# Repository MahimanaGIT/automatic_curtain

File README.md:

<h1 align="center">Automatic Curtain</h1>

<div align="center">
Elevate your home with IoT-enabled smart curtain controller for effortless living
</div>

## ⭐️ Why Automatic Curtain?
Automating blinds can provide convenience and energy efficiency. They can be programmed to open and close at specific times of the day, allowing natural light in to reduce the need of artificial lighting. They can also be controlled remotely, making it easy to adjust the amount of light and privacy in a room without having to physically adjust the blinds. Additionally, automatic blinds can help to regulate the temperature in a room.

## 🔥 Watch the video

<p align="center">
  
</p>

## ✨ Features

- 😎 Easy to set up and integrate
- 📱 Remote control - the ability to open and close the curtains with precision using Alexa app
- 🛡 Safety feature - the ability to detect obstacles and stop the motor to prevent injury or damage to the curtains
- 💅 Manual Override - the ability to manually operate the curtains in case of Alexa not available
- 🚀 Motorized operation - the ability to open and close the curtains using a motor, rather than manual operation
- 📦 Smart home integration - the ability to connect the blinds to other smart home devices such as thermostat using alexa. Provides added convenience and energy efficiency

## 📋 [Doxygen Documentation](https://mahimanagit.github.io/automatic_curtain/)

## 🚀 Getting Started
### For how to use and build your own, refer [🗒 Manual](resources/MANUAL/manual.pdf)
### 👨‍💻 [Coding Style](https://google.github.io/styleguide/cppguide.html)
### Steps to setup for development:
1. Clone the repo
2. Setup clang format:
   - Install clang format extension in VS Code: 
    ```
      Name: Clang-Format
      Id: xaver.clang-format
      Description: Use Clang-Format in Visual Studio Code
      Version: 1.9.0
      Publisher: xaver
      VS Marketplace Link: https://marketplace.visualstudio.com/items?itemName=xaver.clang-format
    ```
   - Add following lines to **settings.json** in your VS Code:
    ```
    "editor.formatOnSave": true
    ```
    Now, everytime you save your code will automatically be formatted according to clang
    
3. Setup ESP32 Arduino Core using [this guide](https://randomnerdtutorials.com/installing-the-esp32-board-in-arduino-ide-windows-instructions/)
   
4. Setup Libraries
   - The link to all the libraries can be found at the end of this page. A compressed folder of all the libraries can be found in the [folder](resources/LIBRARY_ZIP/ac_lib.zip)
   - You can download the libraries using the links or just copy the extracted libraries from the above compressed folder in the **~/Arduino/libraries** or your customized library folder.

### Optional setup for development:
1. Setup doxygen:
   - Install doxygen and graphviz (doxygen uses dot from graphviz to generate graphs):
      ```
      sudo apt-get install doxygen
      sudo apt-get install graphviz 
      ```
   - Currently, the **DOT_PATH** is hardcoded in **Doxyfile** as `/usr/bin/dot` on line no. 2398, one can check if the dot path in their system is same or not by running
      ```
      which dot
      ```
      If the path is different, update it in the doxyfile
   - Generate doxygen files by running the following command in the terminal:
      ```
      doxygen Doxyfile
      ```
    - The files will be available in `doxygen` folder, click on or open `index.html` in **html** folder with any browser and you would be able to browse the documentation

## 🛡️ License

Automatic Curtain is licensed under the MIT License - see the [LICENSE](LICENSE.md) file for details.

## 🗒 References:

Thanks to the following repos for making the journey easier for the project:

1. [AsyncTCP](https://github.com/me-no-dev/AsyncTCP.git)
2. [Fauxmo](https://github.com/vintlabs/fauxmoESP.git)
3. [ESPAsyncWebServer](https://github.com/me-no-dev/ESPAsyncWebServer.git)
4. [FastLED](https://github.com/FastLED/FastLED.git)
5. [TMCStepper](https://github.com/teemuatlut/TMCStepper.gi)

For awesome readme help, referenced [novu](https://github.com/novuhq/novu)

## ✏️ Contributors 

- Dhiraj Deshmukh (deshmukhdhiraj15@gmail.com)
- Mahimana Bhatt (mahimanabhatt@gmail.com)

## 💻 Need Help?

We are more than happy to help you. If you are getting any errors or facing problems while working on this project, join our [slack](https://join.slack.com/t/mad-myj2315/shared_invite/zt-1n3oqsv1z-pdAomyv074gVCvfYfFaRgA) and ask for help. We are open to discussing anything related to the project.

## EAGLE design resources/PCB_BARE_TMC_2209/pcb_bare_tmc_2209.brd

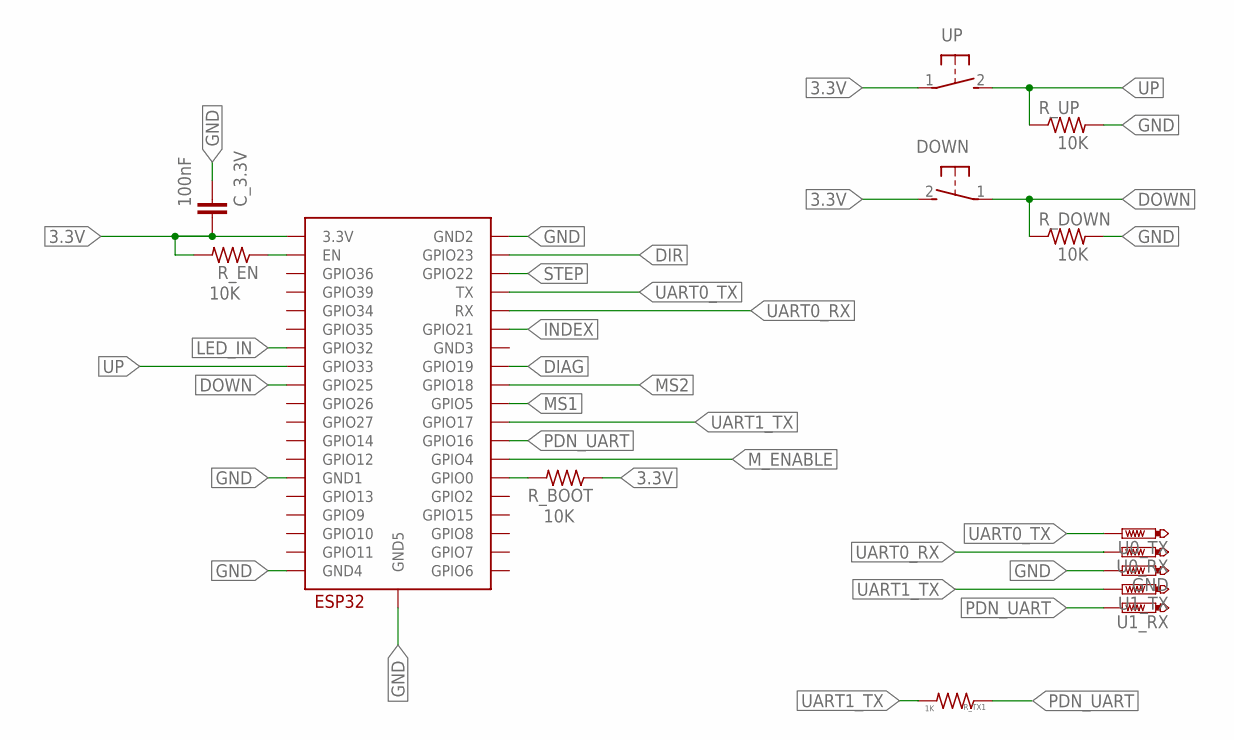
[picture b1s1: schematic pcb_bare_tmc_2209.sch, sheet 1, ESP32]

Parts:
C_3.3V: 100nF; C0805K
DOWN: 31-XX; B3F-31XX
GND: PTR1TP20SQ; TP20SQ
R_BOOT: 10K; R0805
R_DOWN: 10K; R0805
R_EN: 10K; R0805
R_TX1: 1K; R0805
R_UP: 10K; R0805
U0_RX, U0_TX, U1_RX, U1_TX: PTR1TP20SQ; TP20SQ
U$2: ESP32-WROOM
UP: 31-XX; B3F-31XX

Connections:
3.3V: C_3.3V.2, DOWN.2 (S), R_BOOT.1, R_EN.2, U$2.3V3 (3.3V), UP.1; also elsewhere on the board
DIAG: U$2.IO19 (GPIO19); also elsewhere on the board
DIR: U$2.IO23 (GPIO23); also elsewhere on the board
DOWN: DOWN.1, R_DOWN.1, U$2.IO25 (GPIO25)
GND: C_3.3V.1, GND.TP, R_DOWN.2, R_UP.2, U$2.GND1, U$2.GND2, U$2.GND4, U$2.GND5; also elsewhere on the board
INDEX: U$2.IO21 (GPIO21); also elsewhere on the board
LED_IN: U$2.IO32 (GPIO32); also elsewhere on the board
MS1: U$2.IO5 (GPIO5); also elsewhere on the board
MS2: U$2.IO18 (GPIO18); also elsewhere on the board
M_ENABLE: U$2.IO4 (GPIO4); also elsewhere on the board
unnamed: R_BOOT.2, U$2.IO0 (GPIO0)
unnamed: R_EN.1, U$2.EN
PDN_UART: R_TX1.1, U1_RX.TP, U$2.IO16 (GPIO16); also elsewhere on the board
STEP: U$2.IO22 (GPIO22); also elsewhere on the board
UART0_RX: U0_RX.TP, U$2.RX
UART0_TX: U0_TX.TP, U$2.TX
UART1_TX: R_TX1.2, U1_TX.TP, U$2.IO17 (GPIO17)
UP: R_UP.1, U$2.IO33 (GPIO33), UP.2 (S)

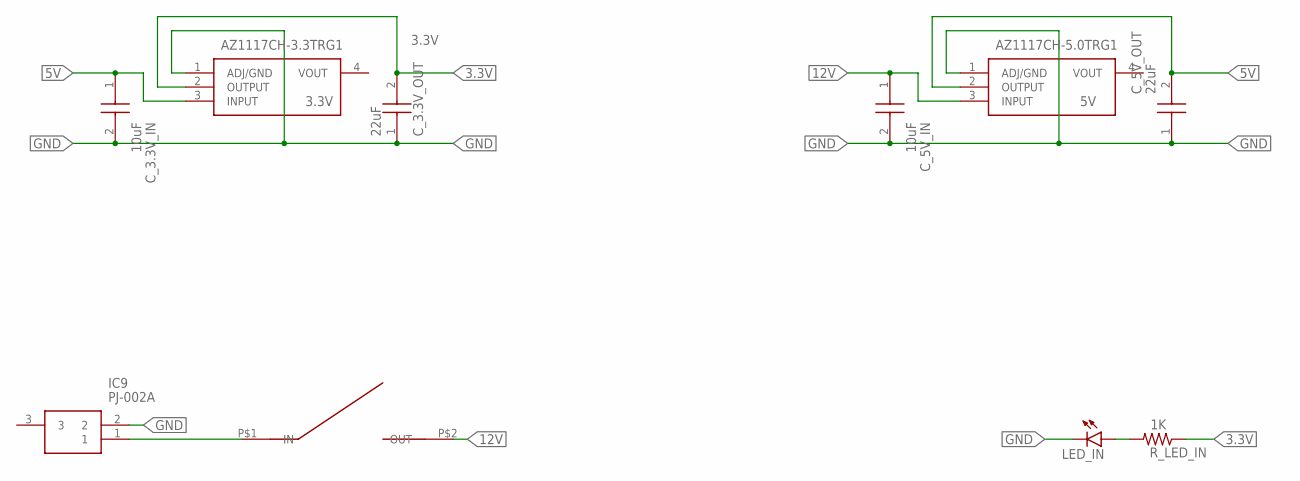
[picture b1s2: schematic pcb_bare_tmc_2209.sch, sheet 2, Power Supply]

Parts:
3.3V: AZ1117CH-3.3TRG1; SOT230P700X180-4N
5V: AZ1117CH-5.0TRG1; SOT230P700X180-4N
C_3.3V_IN, C_5V_IN: 10uF; CAPC2013X95N
C_3.3V_OUT, C_5V_OUT: 22uF; CAPC3216X100N
IC9: PJ-002A; PJ002A
LED_IN: LEDSML0805; SML0805
R_LED_IN: 1K; R0805
U$1: SPSTROCKERSWITCH2PIN; SPST2PINROCKER

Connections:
3.3V: 3.3V.2 (OUTPUT), C_3.3V_OUT.2, R_LED_IN.1; also elsewhere on the board
5V: 3.3V.3 (INPUT), 5V.2 (OUTPUT), C_3.3V_IN.1, C_5V_OUT.2; also elsewhere on the board
12V: 5V.3 (INPUT), C_5V_IN.1, U$1.P$2 (OUT); also elsewhere on the board
GND: 3.3V.1 (ADJ/GND), 5V.1 (ADJ/GND), C_3.3V_IN.2, C_3.3V_OUT.1, C_5V_IN.2, C_5V_OUT.1, IC9.2, LED_IN.C; also elsewhere on the board
unnamed: IC9.1, U$1.P$1 (IN)
unnamed: LED_IN.A, R_LED_IN.2

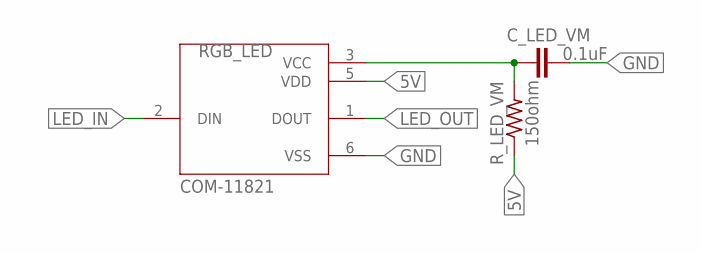
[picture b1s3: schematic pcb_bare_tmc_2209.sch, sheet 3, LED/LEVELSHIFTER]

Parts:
C_LED_VM: 0.1uF; C0805K
RGB_LED: COM-11821; LED_COM-11821
R_LED_VM: 150ohm; R0805

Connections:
5V: RGB_LED.5 (VDD), R_LED_VM.1; also elsewhere on the board
GND: C_LED_VM.2, RGB_LED.6 (VSS); also elsewhere on the board
LED_IN: RGB_LED.2 (DIN); also elsewhere on the board
LED_OUT: RGB_LED.1 (DOUT)
unnamed: C_LED_VM.1, RGB_LED.3 (VCC), R_LED_VM.2

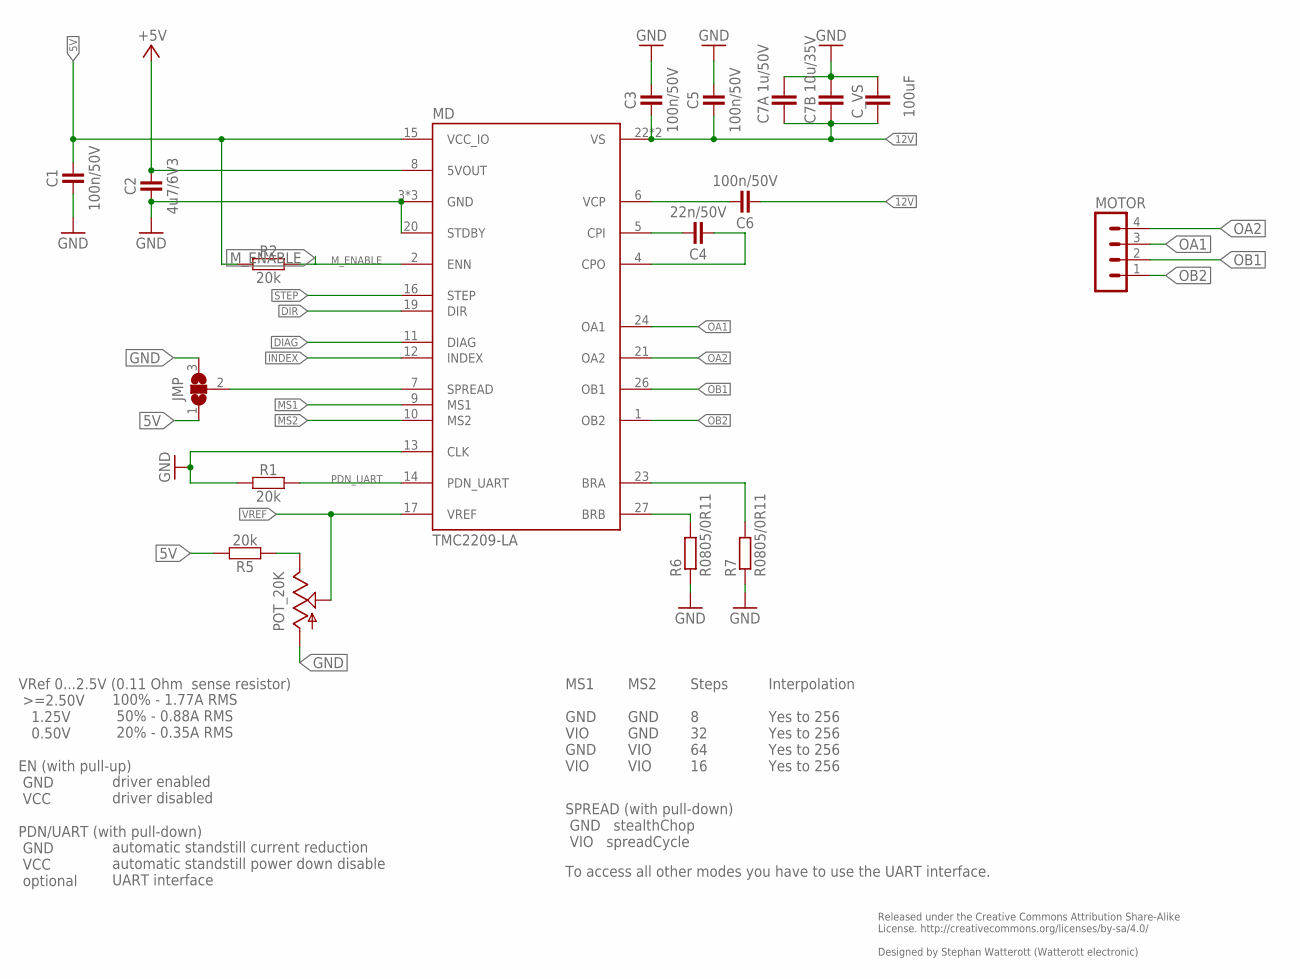
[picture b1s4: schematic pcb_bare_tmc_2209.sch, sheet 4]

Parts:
C1, C3, C5, C6: 100n/50V; C0402
C2: 4u7/6V3; C0402
C4: 22n/50V; C0402
C7A: 1u/50V; C0805
C7B: 10u/35V; C1206
C_VS: 100uF; C2.5-3
JMP: JUMPER3-0402-NC; JUMPER3-0402_NC
MD: TMC2209-LA; QFN28-PAD3.7
MOTOR: MA04-1
POT_20K: TRIM_US-3223G; 3223G
R1, R2, R5: 20k; C0402
R6, R7: R0805/0R11; M0805

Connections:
5V: C1.2, JMP.1, MD.15 (VCC_IO), R2.1, R5.2; also elsewhere on the board
12V: C3.1, C5.1, C6.1, C7A.1, C7B.1, C_VS.1, MD.22 (VS), MD.28 (VS); also elsewhere on the board
+5V: C2.2, MD.8 (5VOUT)
BRA: MD.23 (BRA), R7.2
BRB: MD.27 (BRB), R6.2
CPI: C4.2, MD.5 (CPI)
CPO: C4.1, MD.4 (CPO)
DIAG: MD.11 (DIAG); also elsewhere on the board
DIR: MD.19 (DIR); also elsewhere on the board
GND: C1.1, C2.1, C3.2, C5.2, C7A.2, C7B.2, C_VS.2, JMP.3, MD.3 (GND), MD.13 (CLK), MD.18 (GND), MD.20 (STDBY), MD.TP (GND), POT_20K.1 (A), R1.1, R6.1, R7.1; also elsewhere on the board
INDEX: MD.12 (INDEX); also elsewhere on the board
MS1: MD.9 (MS1); also elsewhere on the board
MS2: MD.10 (MS2); also elsewhere on the board
M_ENABLE: MD.2 (ENN), R2.2; also elsewhere on the board
unnamed: JMP.2, MD.7 (SPREAD)
OA1: MD.24 (OA1), MOTOR.3
OA2: MD.21 (OA2), MOTOR.4
OB1: MD.26 (OB1), MOTOR.2
OB2: MD.1 (OB2), MOTOR.1
PDN_UART: MD.14 (PDN_UART), R1.2; also elsewhere on the board
STEP: MD.16 (STEP); also elsewhere on the board
VCP: C6.2, MD.6 (VCP)
VREF: MD.17 (VREF), POT_20K.2 (S)
VREF1: POT_20K.3 (E), R5.1

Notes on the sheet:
Released under the Creative Commons Attribution Share-Alike License. http://creativecommons.org/licenses/by-sa/4.0/ Designed by Stephan Watterott (Watterott electronic)
VRef 0...2.5V (0.11 Ohm sense resistor) >=2.50V 1.25V 0.50V EN (with pull-up) GND VCC PDN/UART (with pull-down) GND VCC optional
100% - 1.77A RMS 50% - 0.88A RMS 20% - 0.35A RMS driver enabled driver disabled automatic standstill current reduction automatic standstill power down disable UART interface
MS1 GND VIO GND VIO
MS2 GND GND VIO VIO
Steps 8 32 64 16
Interpolation Yes to 256 Yes to 256 Yes to 256 Yes to 256
SPREAD (with pull-down) GND stealthChop VIO spreadCycle
To access all other modes you have to use the UART interface.

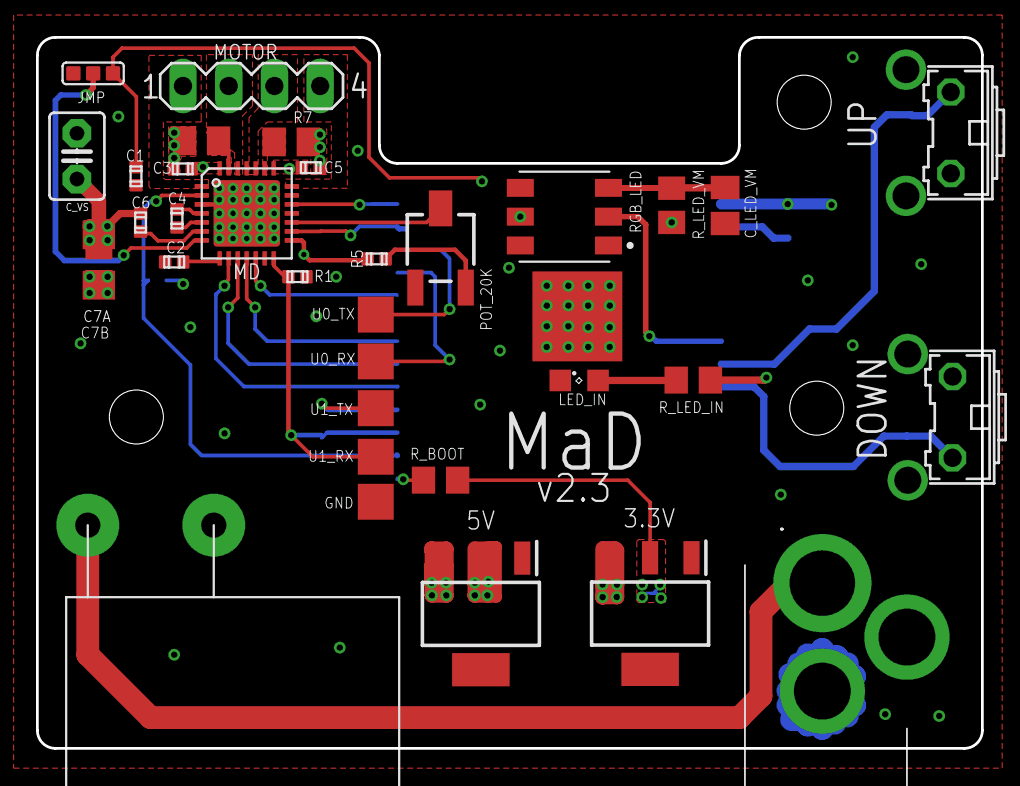
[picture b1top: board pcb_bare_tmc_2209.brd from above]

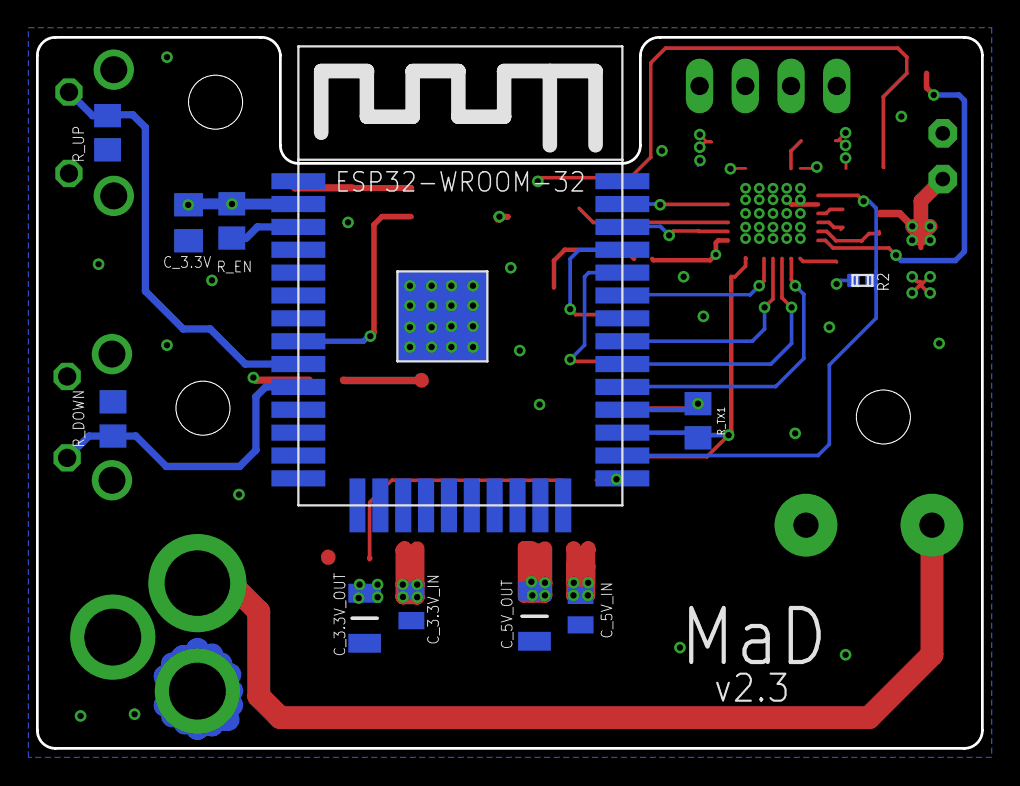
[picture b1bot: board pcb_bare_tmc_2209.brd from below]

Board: 4 copper layers, 52.5 x 39.5 mm, 45 parts (11 on the bottom side), 36 nets.

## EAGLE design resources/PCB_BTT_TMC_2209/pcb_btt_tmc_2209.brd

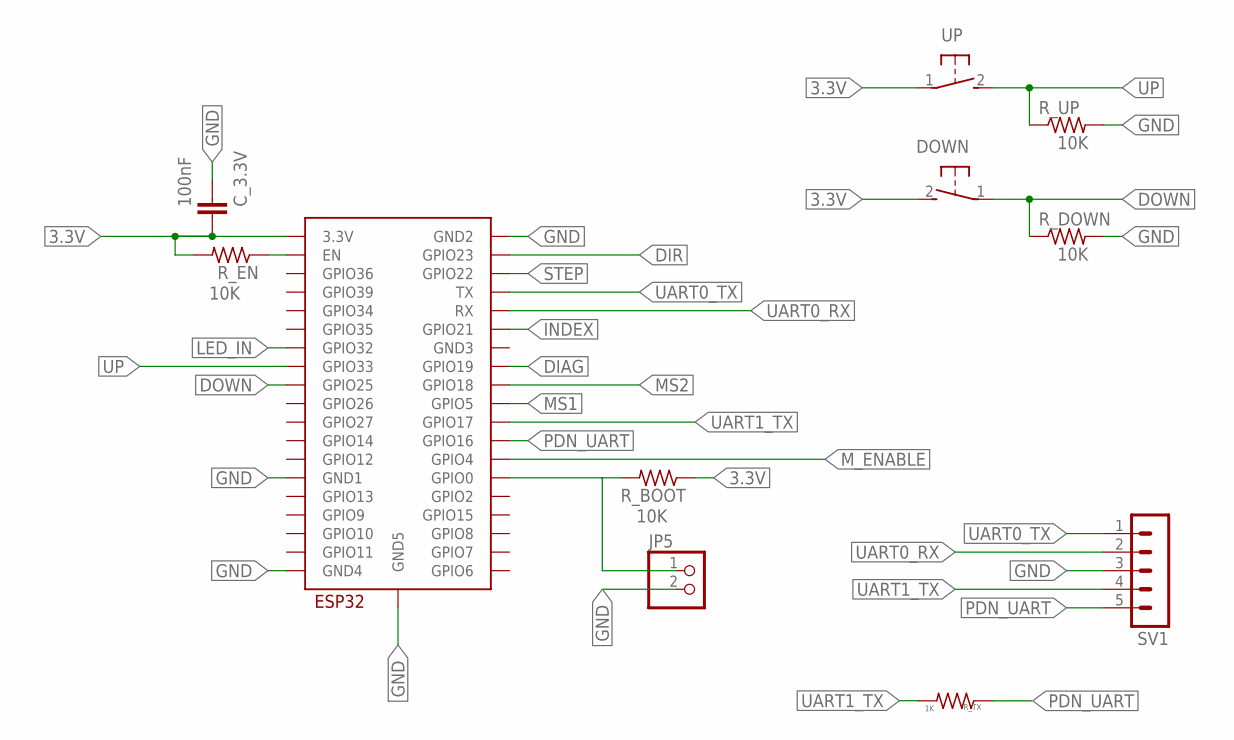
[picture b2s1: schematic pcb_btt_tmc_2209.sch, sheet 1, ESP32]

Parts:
C_3.3V: 100nF; C0805K
DOWN: 31-XX; B3F-31XX
JP5: PINHD-1X2; 1X02
R_BOOT: 10K; R0805
R_DOWN: 10K; R0805
R_EN: 10K; R0805
R_TX: 1K; R0805
R_UP: 10K; R0805
SV1: MA05-1
U$2: ESP32-WROOM
UP: 31-XX; B3F-31XX

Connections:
3.3V: C_3.3V.2, DOWN.2 (S), R_BOOT.1, R_EN.2, U$2.3V3 (3.3V), UP.1; also elsewhere on the board
DIAG: U$2.IO19 (GPIO19); also elsewhere on the board
DIR: U$2.IO23 (GPIO23); also elsewhere on the board
DOWN: DOWN.1, R_DOWN.1, U$2.IO25 (GPIO25)
GND: C_3.3V.1, JP5.2, R_DOWN.2, R_UP.2, SV1.3, U$2.GND1, U$2.GND2, U$2.GND4, U$2.GND5; also elsewhere on the board
INDEX: U$2.IO21 (GPIO21); also elsewhere on the board
LED_IN: U$2.IO32 (GPIO32); also elsewhere on the board
MS1: U$2.IO5 (GPIO5); also elsewhere on the board
MS2: U$2.IO18 (GPIO18); also elsewhere on the board
M_ENABLE: U$2.IO4 (GPIO4); also elsewhere on the board
unnamed: JP5.1, R_BOOT.2, U$2.IO0 (GPIO0)
unnamed: R_EN.1, U$2.EN
PDN_UART: R_TX.1, SV1.5, U$2.IO16 (GPIO16); also elsewhere on the board
STEP: U$2.IO22 (GPIO22); also elsewhere on the board
UART0_RX: SV1.2, U$2.RX
UART0_TX: SV1.1, U$2.TX
UART1_TX: R_TX.2, SV1.4, U$2.IO17 (GPIO17)
UP: R_UP.1, U$2.IO33 (GPIO33), UP.2 (S)

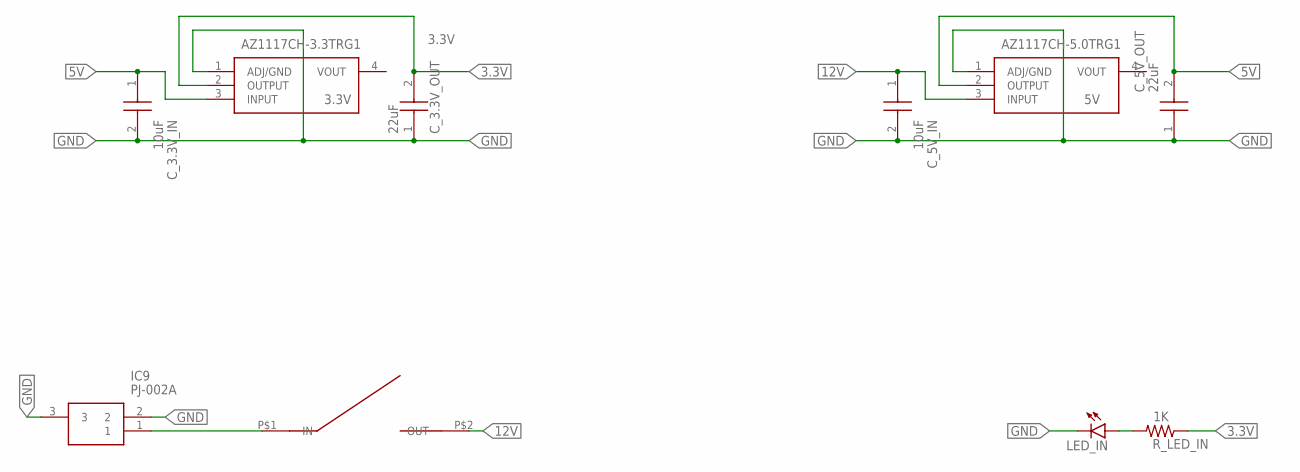
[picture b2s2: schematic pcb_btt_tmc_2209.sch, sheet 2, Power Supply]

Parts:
3.3V: AZ1117CH-3.3TRG1; SOT230P700X180-4N
5V: AZ1117CH-5.0TRG1; SOT230P700X180-4N
C_3.3V_IN, C_5V_IN: 10uF; CAPC2013X95N
C_3.3V_OUT, C_5V_OUT: 22uF; CAPC3216X100N
IC9: PJ-002A; PJ002A
LED_IN: LEDSML0805; SML0805
R_LED_IN: 1K; R0805
U$1: SPSTROCKERSWITCH2PIN; SPST2PINROCKER

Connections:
3.3V: 3.3V.2 (OUTPUT), C_3.3V_OUT.2, R_LED_IN.1; also elsewhere on the board
5V: 3.3V.3 (INPUT), 5V.2 (OUTPUT), C_3.3V_IN.1, C_5V_OUT.2; also elsewhere on the board
12V: 5V.3 (INPUT), C_5V_IN.1, U$1.P$2 (OUT); also elsewhere on the board
GND: 3.3V.1 (ADJ/GND), 5V.1 (ADJ/GND), C_3.3V_IN.2, C_3.3V_OUT.1, C_5V_IN.2, C_5V_OUT.1, IC9.2, IC9.3, LED_IN.C; also elsewhere on the board
unnamed: IC9.1, U$1.P$1 (IN)
unnamed: LED_IN.A, R_LED_IN.2

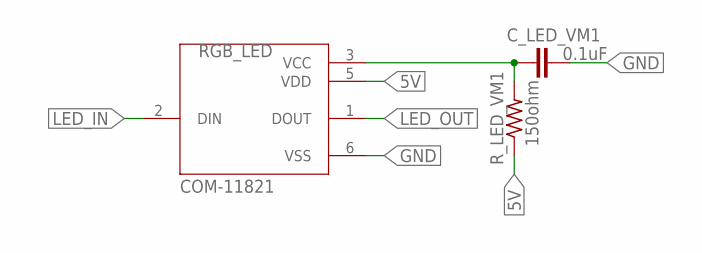
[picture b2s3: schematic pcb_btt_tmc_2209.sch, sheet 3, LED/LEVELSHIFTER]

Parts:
C_LED_VM1: 0.1uF; C0805K
RGB_LED: COM-11821; LED_COM-11821
R_LED_VM1: 150ohm; R0805

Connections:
5V: RGB_LED.5 (VDD), R_LED_VM1.1; also elsewhere on the board
GND: C_LED_VM1.2, RGB_LED.6 (VSS); also elsewhere on the board
LED_IN: RGB_LED.2 (DIN); also elsewhere on the board
LED_OUT: RGB_LED.1 (DOUT)
unnamed: C_LED_VM1.1, RGB_LED.3 (VCC), R_LED_VM1.2

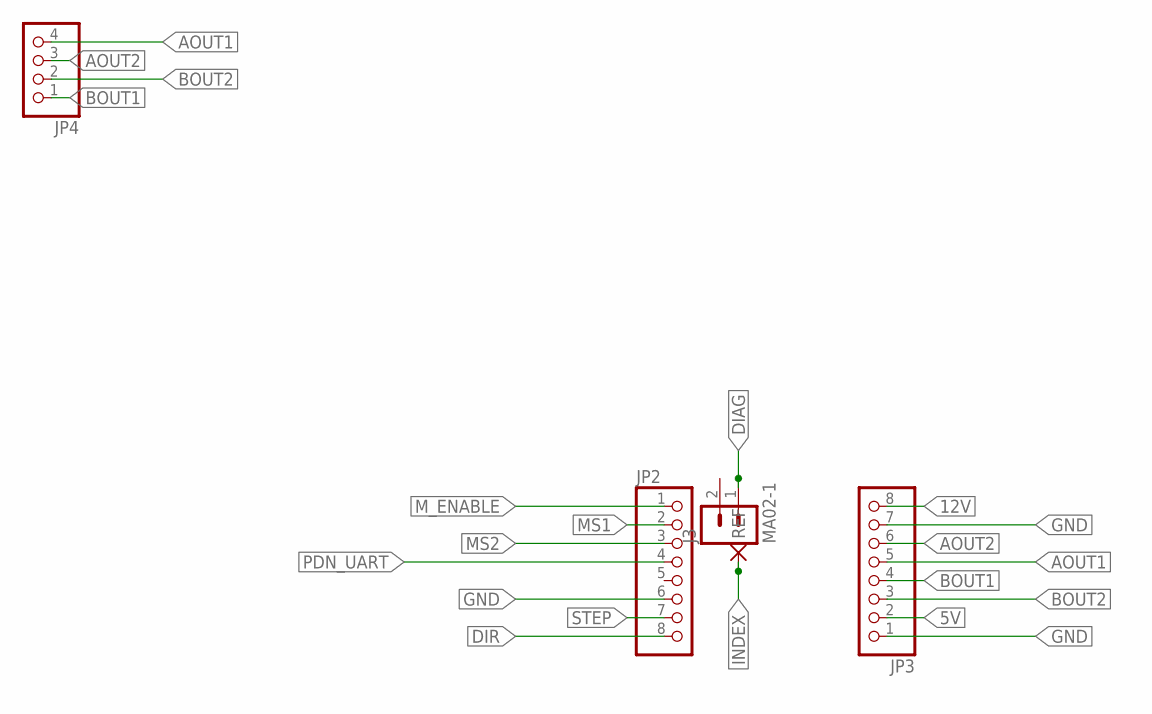
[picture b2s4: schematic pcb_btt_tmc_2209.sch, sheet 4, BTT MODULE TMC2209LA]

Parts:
J3: MA02-1
JP2, JP3: PINHD-1X8; 1X08
JP4: PINHD-1X4; 1X04
REF: PAD-0.6-1.1

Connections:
5V: JP3.2; also elsewhere on the board
12V: JP3.8; also elsewhere on the board
AOUT1: JP3.5, JP4.4
AOUT2: JP3.6, JP4.3
BOUT1: JP3.4, JP4.1
BOUT2: JP3.3, JP4.2
DIAG: J3.1; also elsewhere on the board
DIR: JP2.8; also elsewhere on the board
GND: JP2.6, JP3.1, JP3.7; also elsewhere on the board
INDEX: REF.1; also elsewhere on the board
MS1: JP2.2; also elsewhere on the board
MS2: JP2.3; also elsewhere on the board
M_ENABLE: JP2.1; also elsewhere on the board
PDN_UART: JP2.4; also elsewhere on the board
STEP: JP2.7; also elsewhere on the board

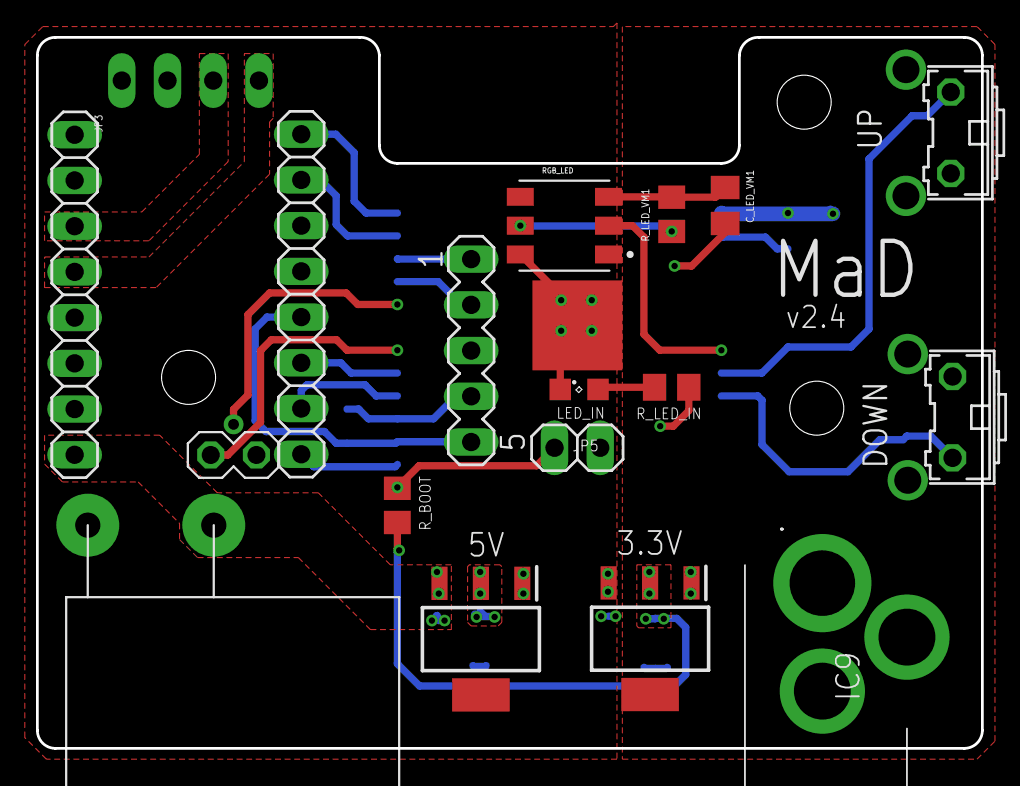
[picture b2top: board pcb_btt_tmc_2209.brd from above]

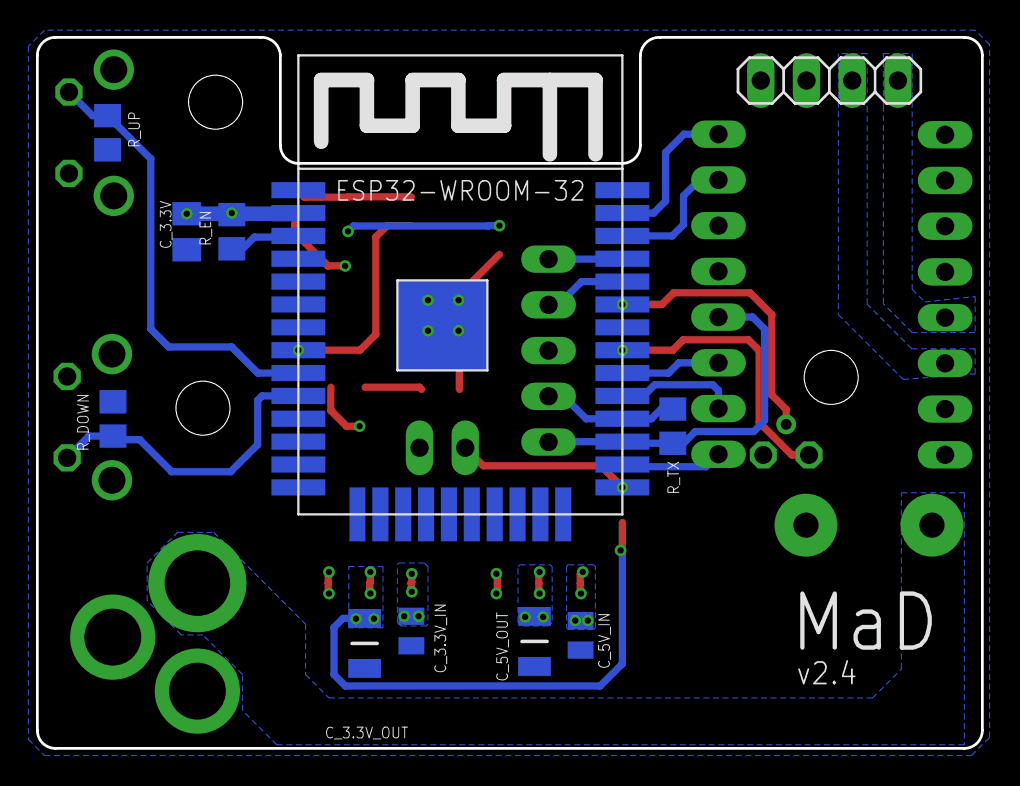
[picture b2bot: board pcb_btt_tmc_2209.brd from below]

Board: 2 copper layers, 52.5 x 39.5 mm, 29 parts (11 on the bottom side), 27 nets.

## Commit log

2022-07-18 Removing .vscode
2022-07-20 Initial repo/code structure with Doxygen
2022-07-22 Removing reproducible doxygen files
2022-07-24 Updating readme to install and use clang and doxygen, adding .gitignore
2022-08-04 AC-108: Define code structure
2022-08-13 AC-115: Implement Logging Class
2022-08-13 AC-113: Implement Internal Storage
2022-08-13 AC-114: Implement Indicator Class
2022-08-14 AC-116: Implement connectivity class
2022-08-16 AC-122: Implement Alexa Interaction
2022-10-17 AC-131: Adding Final PCB Files
2022-10-30 AC-129: Implement Motor Driver
2022-11-05 AC-121: Implement Manual Interaction
2022-11-05 AC-130: Implemented controller
2022-11-06 AC-150: Indicator changes according to mode
2022-11-06 AC-146: Controller bugfix for starting motor for blind traversal
2022-11-11 Removing soft traversal, porting motor driver handler to separate thread
2022-11-11 Removing stall value from calibration params
2022-11-11 Removing reset driver function
2022-11-11 Updating non stall detection
2022-11-11 Started calibration implementation
2022-11-12 Calibration implemented
2022-11-12 Fixing number of steps calculation
2022-11-12 Updating total step count to max value
2022-11-13 AC-151: Restart if in maintainence or reset mode for long time
2022-11-13 Updating reset mode start
2022-11-14 Convert webserver to unique ptr
2022-11-16 AC-154: Resolved MR comments, connectivity and controller updated. Set state Alexa
2023-01-14 AC-121: Implemented manual interaction, bugfixes and new features
2023-01-14 Moving doxygen
2023-01-14 Moving files for hosting on github pages
2023-01-14 Empty folders
2023-01-14 Including BOM for PCBs
2023-01-15 Adding_architecture_html
2023-01-15 Adding folders, licence
2023-01-15 Updating readme
2023-01-15 Adding place holder manual
2023-01-15 Correcting icons
2023-01-16 Adding mechanical parts to order
2023-01-16 First version of manual
2023-01-16 Final Mechanical Parts
2023-01-16 Updating docker setup readme
2023-01-16 Added solidworks file zip folder and added contributors to readme
2023-01-16 Updating readme and remove duplicate file
